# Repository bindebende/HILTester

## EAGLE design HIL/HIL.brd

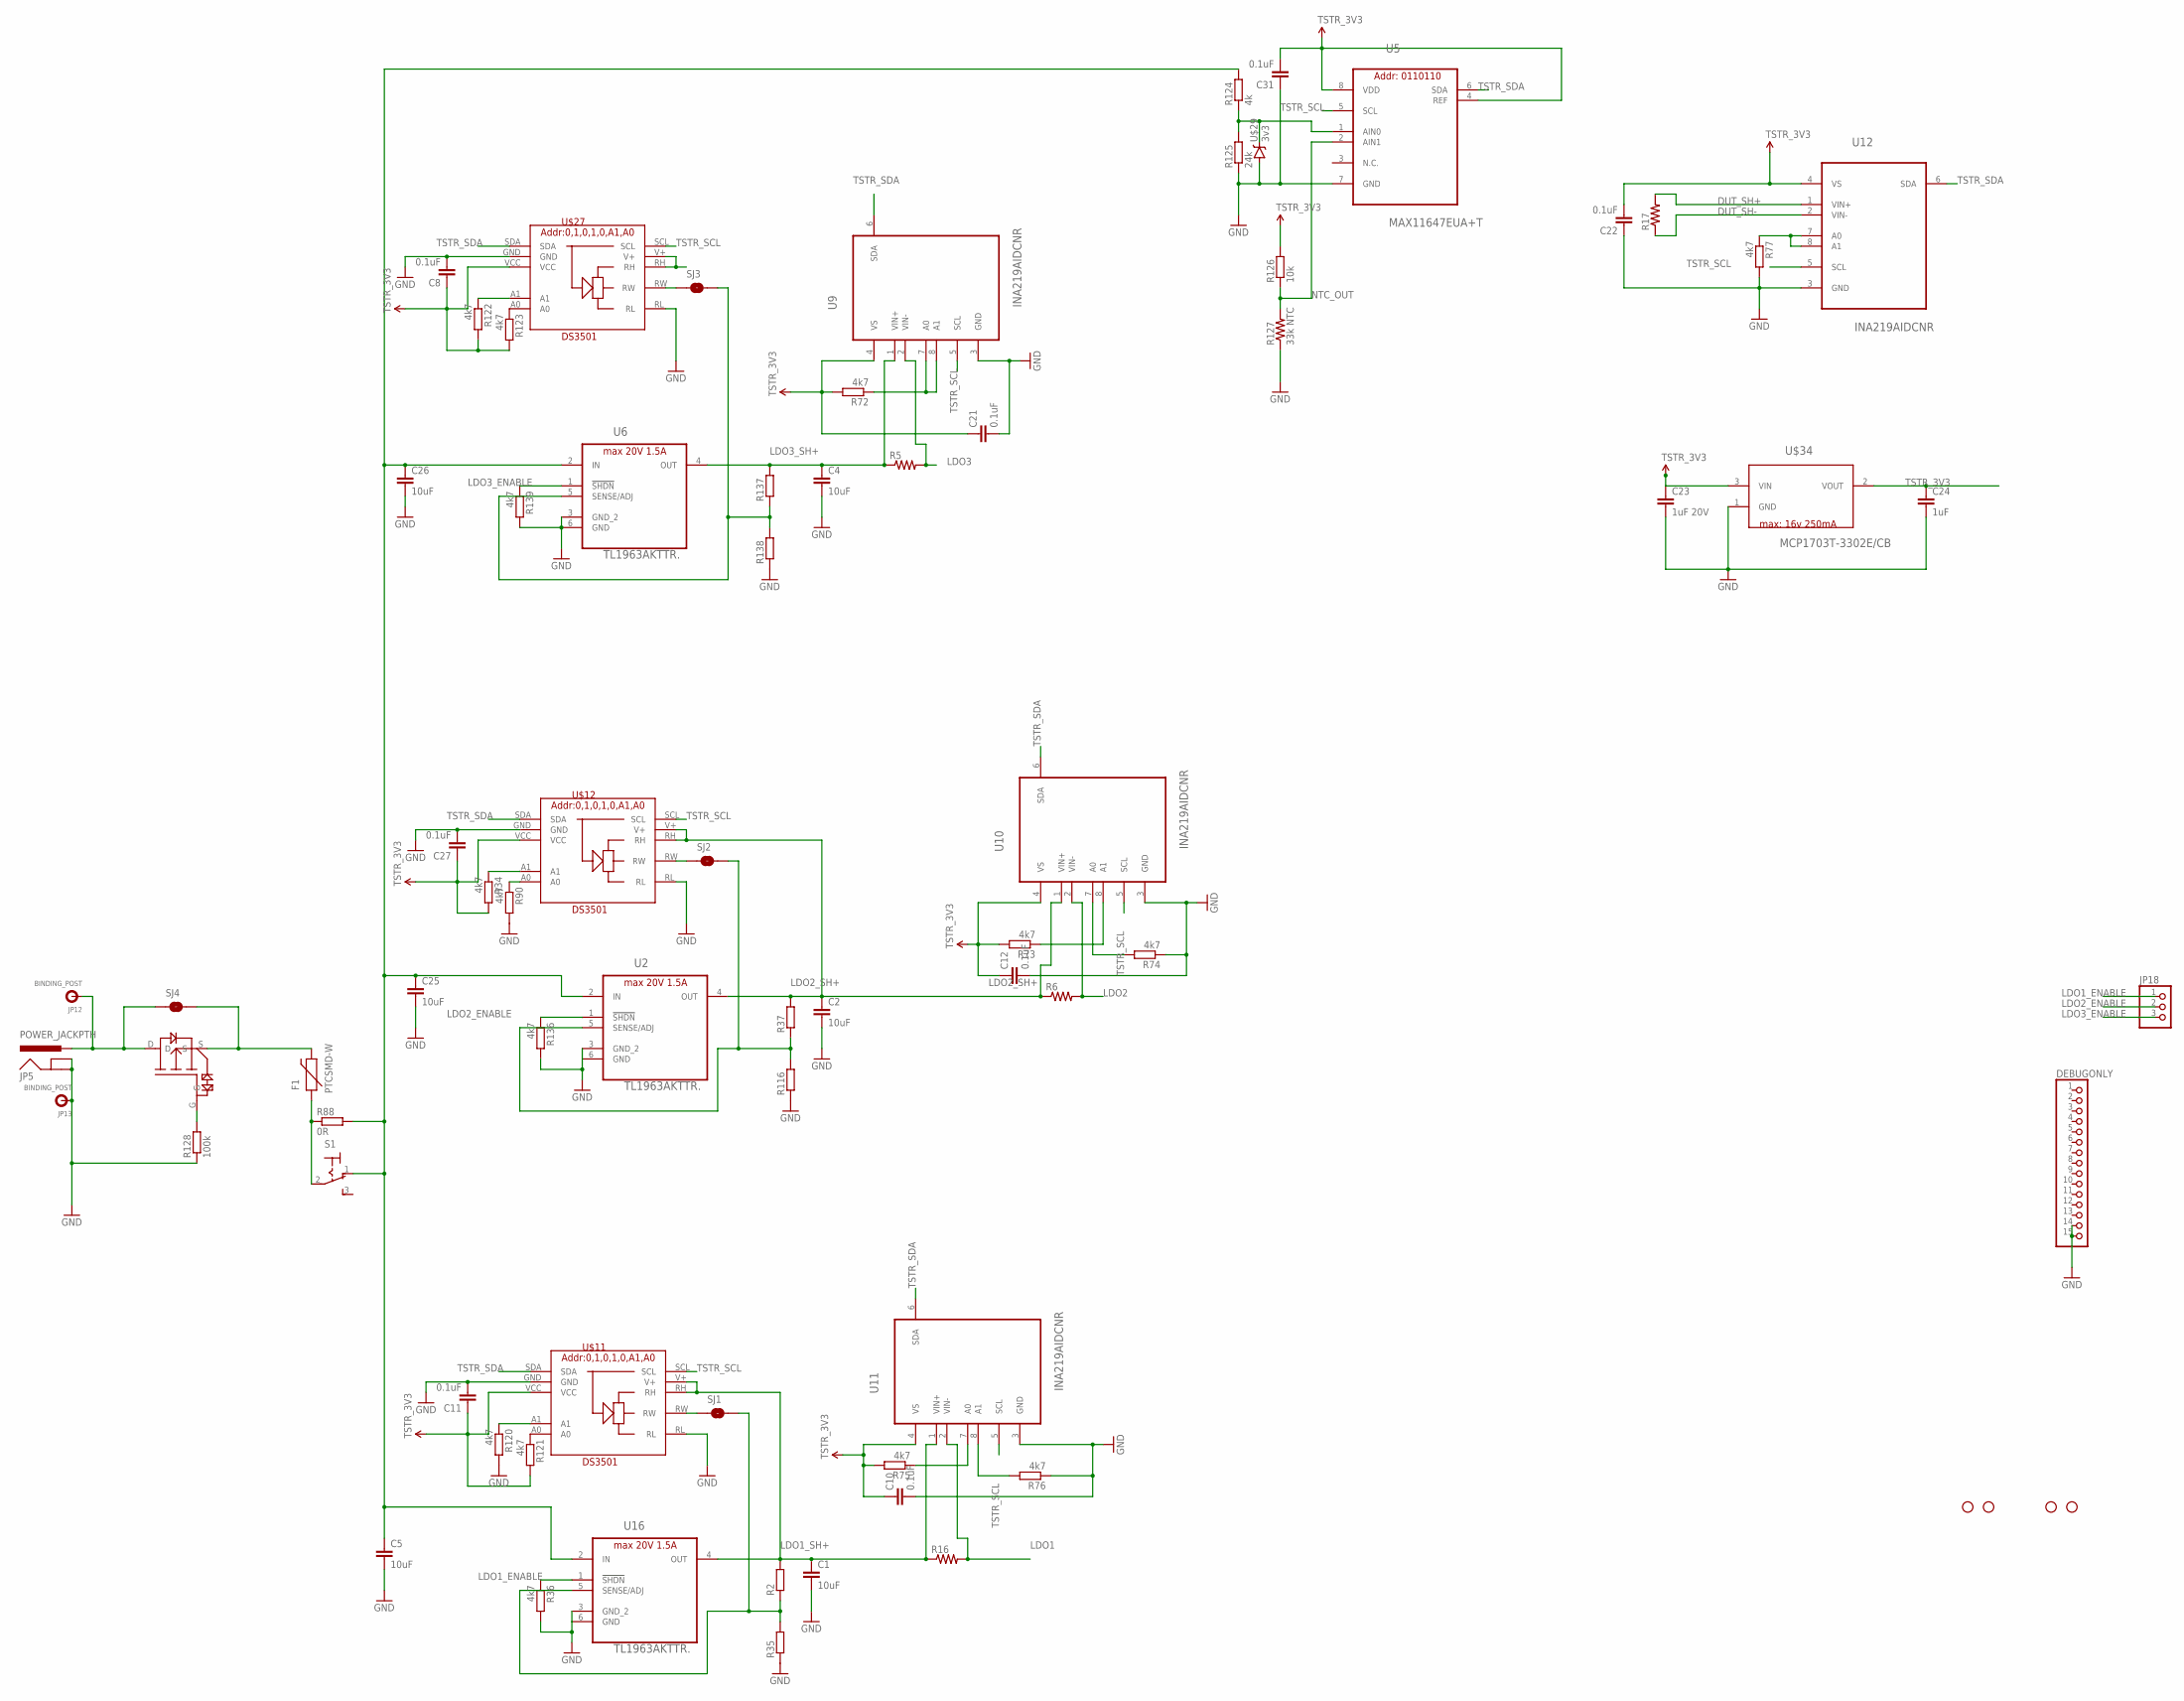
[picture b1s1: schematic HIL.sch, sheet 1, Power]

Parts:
C1, C2, C4, C5, C25, C26: 10uF; C0402
C8, C10, C11, C12, C21, C22, C27, C31: 0.1uF; C0402
C23: 1uF 20V; C0402
C24: 1uF; C0402
DEBUGONLY: PINHD-1X15; 1X15
F1: PTCSMD-W; PTC-1206-WIDE
JP5: POWER_JACKPTH; POWER_JACK_PTH
JP12, JP13: BINDING_POST
JP18: PINHD-1X3CB; 1X03-CLEANBIG
R2, R35, R37, R116, R137, R138: R-EU_R0402; R0402
R5, R6, R16, R17: R-US_R5025; R5025
R34, R36, R72, R73, R74, R75, R76, R77, R90, R120, R121, R122, R123, R136, R139: 4k7; R0402
R88: 0R; R0402
R124: 4k; R0402
R125: 24k; R0402
R126: 10k; R0402
R127: 33k NTC; 1206
R128: 100k; R0402
S1: 320-916
SJ1, SJ2, SJ3, SJ4: SOLDERJUMPERROUND; SJ_ROUND
STANDOFF2, STANDOFF3, STANDOFF4, STANDOFF6: STAND-OFF
U2, U6, U16: TL1963AKTTR.; TO170P1485X457-6N
U5: MAX11647EUA+T; SOP65P490X110-8N
U9, U10, U11, U12: INA219AIDCNR; SOT65P280X145-8N
U$11, U$12, U$27: DS3501
U$29: 3v3; SOT23-3
U$31: ATP101; ATPACK
U$34: MCP1703T-3302E/CB; SOT95P300X145-3N

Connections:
AS: R72.1, U9.7 (A0), U9.8 (A1)
DUT_SH+: R17.2, U12.1 (VIN+); also elsewhere on the board
DUT_SH-: R17.1, U12.2 (VIN-); also elsewhere on the board
GND: C1.2, C2.2, C4.2, C5.2, C8.2, C10.2, C11.2, C12.2, C21.2, C22.1, C23.2, C24.2, C25.2, C26.2, C27.2, C31.1, DEBUGONLY.14, DEBUGONLY.15, JP5.GND, JP5.GNDBREAK, JP13.P$1, R35.1, R36.2, R74.1, R76.1, R77.2, R90.2, R116.1, R120.2, R125.1, R127.1, R128.1, R136.2, R138.1, R139.2, U2.3 (GND_2), U2.6 (GND), U5.7 (GND), U6.3 (GND_2), U6.6 (GND), U9.3 (GND), U10.3 (GND), U11.3 (GND), U12.3 (GND), U16.3 (GND_2), U16.6 (GND), U$11.GND, U$11.RL, U$12.GND, U$12.RL, U$27.GND, U$27.RL, U$29.2 (A), U$34.1 (GND); also elsewhere on the board
LDO1: R16.2, U11.2 (VIN-); also elsewhere on the board
LDO1_ADJ: R2.1, R35.2, SJ1.2, U16.5 (SENSE/ADJ)
LDO1_ENABLE: JP18.1, R36.1, U16.1 (!SHDN)
LDO1_RW: SJ1.1, U$11.RW
LDO1_SH+: C1.1, R2.2, R16.1, U11.1 (VIN+), U16.4 (OUT), U$11.RH, U$11.V+; also elsewhere on the board
LDO2: R6.2, U10.2 (VIN-); also elsewhere on the board
LDO2_ADJ: R37.1, R116.2, SJ2.2, U2.5 (SENSE/ADJ)
LDO2_ENABLE: JP18.2, R136.1, U2.1 (!SHDN)
LDO2_RW: SJ2.1, U$12.RW
LDO2_SH+: C2.1, R6.1, R37.2, U2.4 (OUT), U10.1 (VIN+), U$12.RH, U$12.V+; also elsewhere on the board
LDO3: R5.2, U9.2 (VIN-); also elsewhere on the board
LDO3_ADJ: R137.1, R138.2, SJ3.2, U6.5 (SENSE/ADJ)
LDO3_ENABLE: JP18.3, R139.1, U6.1 (!SHDN)
LDO3_RW: SJ3.1, U$27.RW
LDO3_SH+: C4.1, R5.1, R137.2, U6.4 (OUT), U9.1 (VIN+); also elsewhere on the board
unnamed: F1.1, R88.1, S1.2
unnamed: R128.2, U$31.G
unnamed: R73.1, U10.8 (A1)
unnamed: R75.1, U11.7 (A0)
unnamed: R74.2, U10.7 (A0)
unnamed: R76.2, U11.8 (A1)
unnamed: R77.1, U12.7 (A0), U12.8 (A1)
unnamed: R120.1, U$11.A1
unnamed: R121.1, U$11.A0
unnamed: R34.1, U$12.A1
unnamed: R90.1, U$12.A0
unnamed: R122.1, U$27.A1
unnamed: R123.1, U$27.A0
unnamed: U$27.RH, U$27.V+
NTC_OUT: R126.1, R127.2, U5.2 (AIN1)
POWER_IN_12V: C5.1, C23.1, C25.1, C26.1, R88.2, R124.2, S1.1 (O), U2.2 (IN), U6.2 (IN), U16.2 (IN), U$34.3 (VIN); also elsewhere on the board
SUPPLY_DIV: R124.1, R125.2, U5.1 (AIN0), U$29.1 (C)
TSTR_3V3: C8.1, C10.1, C11.1, C12.1, C21.1, C22.2, C24.1, C27.1, C31.2, R34.2, R72.2, R73.2, R75.2, R121.2, R122.2, R123.2, R126.2, U5.4 (REF), U5.8 (VDD), U9.4 (VS), U10.4 (VS), U11.4 (VS), U12.4 (VS), U$11.VCC, U$12.VCC, U$27.VCC, U$34.2 (VOUT); also elsewhere on the board
TSTR_SCL: U5.5 (SCL), U9.5 (SCL), U10.5 (SCL), U11.5 (SCL), U12.5 (SCL), U$11.SCL, U$12.SCL, U$27.SCL; also elsewhere on the board
TSTR_SDA: U5.6 (SDA), U9.6 (SDA), U10.6 (SDA), U11.6 (SDA), U12.6 (SDA), U$11.SDA, U$12.SDA, U$27.SDA; also elsewhere on the board
VIN: F1.2, SJ4.2, U$31.S
VIN_REV: JP5.PWR, JP12.P$1, SJ4.1, U$31.D

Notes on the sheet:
max: 16v 250mA

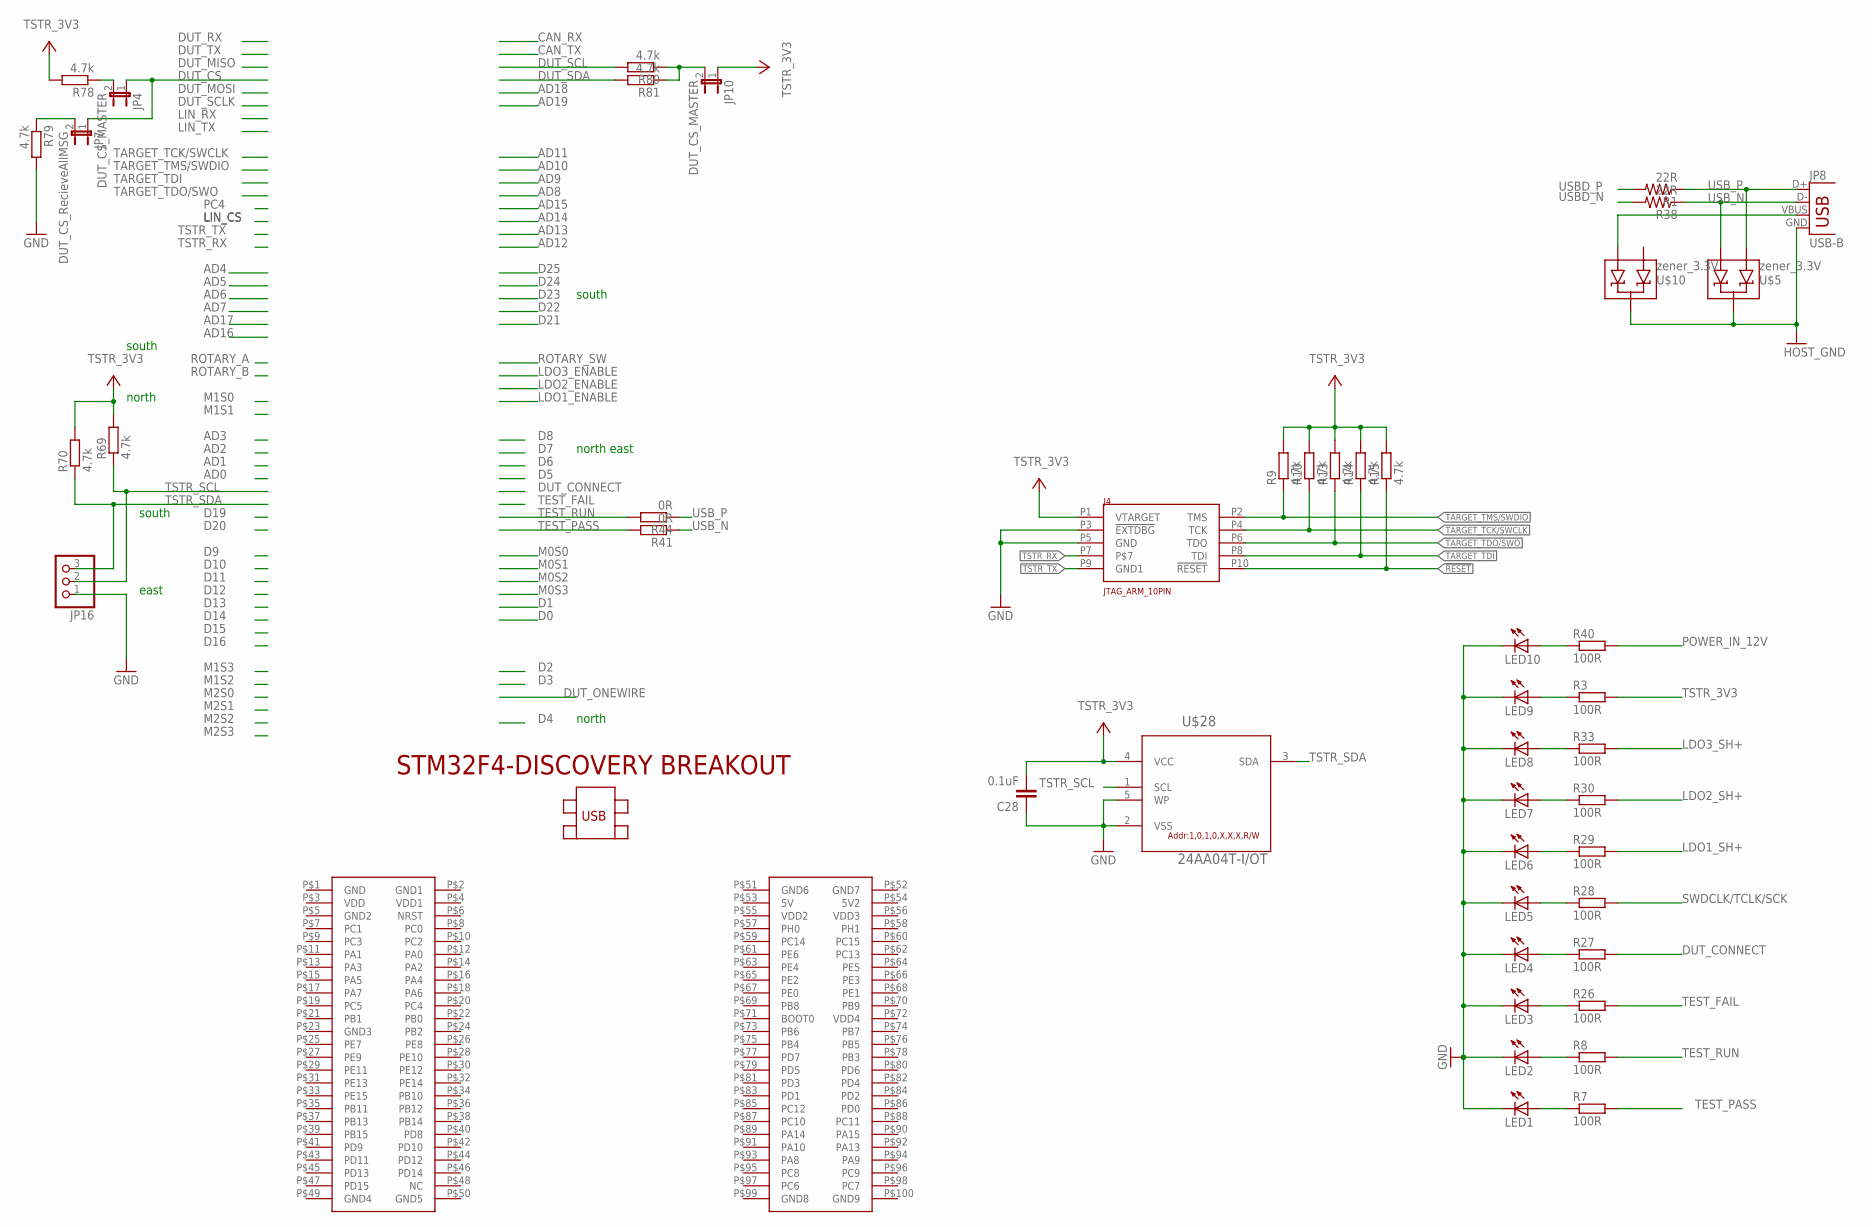
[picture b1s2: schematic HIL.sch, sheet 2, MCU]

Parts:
C28: 0.1uF; C0402K
J4: JTAG_ARM_10PIN; CON_2X5_50MIL
JP4, JP10: DUT_CS_MASTER; SJ_2S-NO
JP7: DUT_CS_RecieveAllMSG; SJ_2S-NO
JP8: USB-B; USB-B-PTH
JP16: PINHD-1X3CB; 1X03-CLEANBIG
LED1, LED2, LED3, LED4, LED5, LED6, LED7, LED8, LED9, LED10: LEDCHIP-LED0805; CHIP-LED0805
R1, R38: 22R; 0402-RES
R3, R7, R8, R26, R27, R28, R29, R30, R33, R40: 100R; R0402
R9, R10, R13, R14, R15, R69, R70, R78, R79, R80, R81: 4.7k; R0402
R41, R44: 0R; R0402
U$5, U$10: zener_3.3V; SOT23-3
U$28: 24AA04T-I/OT; SOT95P290X145-5N
U$30: STM32F4-DISCOVERY_STM32F4-DISCOVERY

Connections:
!RESET: J4.P10 (!RESET), R15.1
DUT_CONNECT: R27.2
DUT_CS: JP4.1, JP7.1; also elsewhere on the board
DUT_SCL: R80.2; also elsewhere on the board
DUT_SDA: R81.2; also elsewhere on the board
GND: C28.1, J4.P3 (!EXTDBG), J4.P5 (GND), JP16.1, LED1.C, LED2.C, LED3.C, LED4.C, LED5.C, LED6.C, LED7.C, LED8.C, LED9.C, LED10.C, R79.2, U$28.2 (VSS), U$28.5 (WP); also elsewhere on the board
HOST_GND: JP8.GND, U$5.3 (C), U$10.3 (C)
LDO1_SH+: R29.2; also elsewhere on the board
LDO2_SH+: R30.2; also elsewhere on the board
LDO3_SH+: R33.2; also elsewhere on the board
unnamed: LED2.A, R8.1
unnamed: LED1.A, R7.1
unnamed: LED3.A, R26.1
unnamed: LED4.A, R27.1
unnamed: LED5.A, R28.1
unnamed: LED6.A, R29.1
unnamed: LED7.A, R30.1
unnamed: LED8.A, R33.1
unnamed: JP7.2, R79.1
unnamed: JP10.2, R80.1, R81.1
unnamed: JP8.VBUS, U$10.1 (A1)
unnamed: LED9.A, R3.1
unnamed: LED10.A, R40.1
POWER_IN_12V: R40.2; also elsewhere on the board
SWDCLK/TCLK/SCK: R28.2; also elsewhere on the board
TARGET_TCK/SWCLK: J4.P4 (TCK), R10.1
TARGET_TDI: J4.P8 (TDI), R14.1
TARGET_TDO/SWO: J4.P6 (TDO), R13.1
TARGET_TMS/SWDIO: J4.P2 (TMS), R9.1
TEST_FAIL: R26.2
TEST_PASS: R7.2, R41.2
TEST_RUN: R8.2, R44.2
TSTR_3V3: C28.2, J4.P1 (VTARGET), JP10.1, R3.2, R9.2, R10.2, R13.2, R14.2, R15.2, R69.2, R70.2, R78.2, U$28.4 (VCC); also elsewhere on the board
TSTR_RX: J4.P7
TSTR_SCL: JP16.2, R69.1, U$28.1 (SCL); also elsewhere on the board
TSTR_SCL1: JP4.2, R78.1
TSTR_SDA: JP16.3, R70.1, U$28.3 (SDA); also elsewhere on the board
TSTR_TX: J4.P9 (GND1)
USBD_N: R38.2
USBD_P: R1.2
USB_N: JP8.D-, R38.1, R41.1, U$5.1 (A1)
USB_P: JP8.D+, R1.1, R44.1, U$5.2 (A2)

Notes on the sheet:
south
north east
north
east

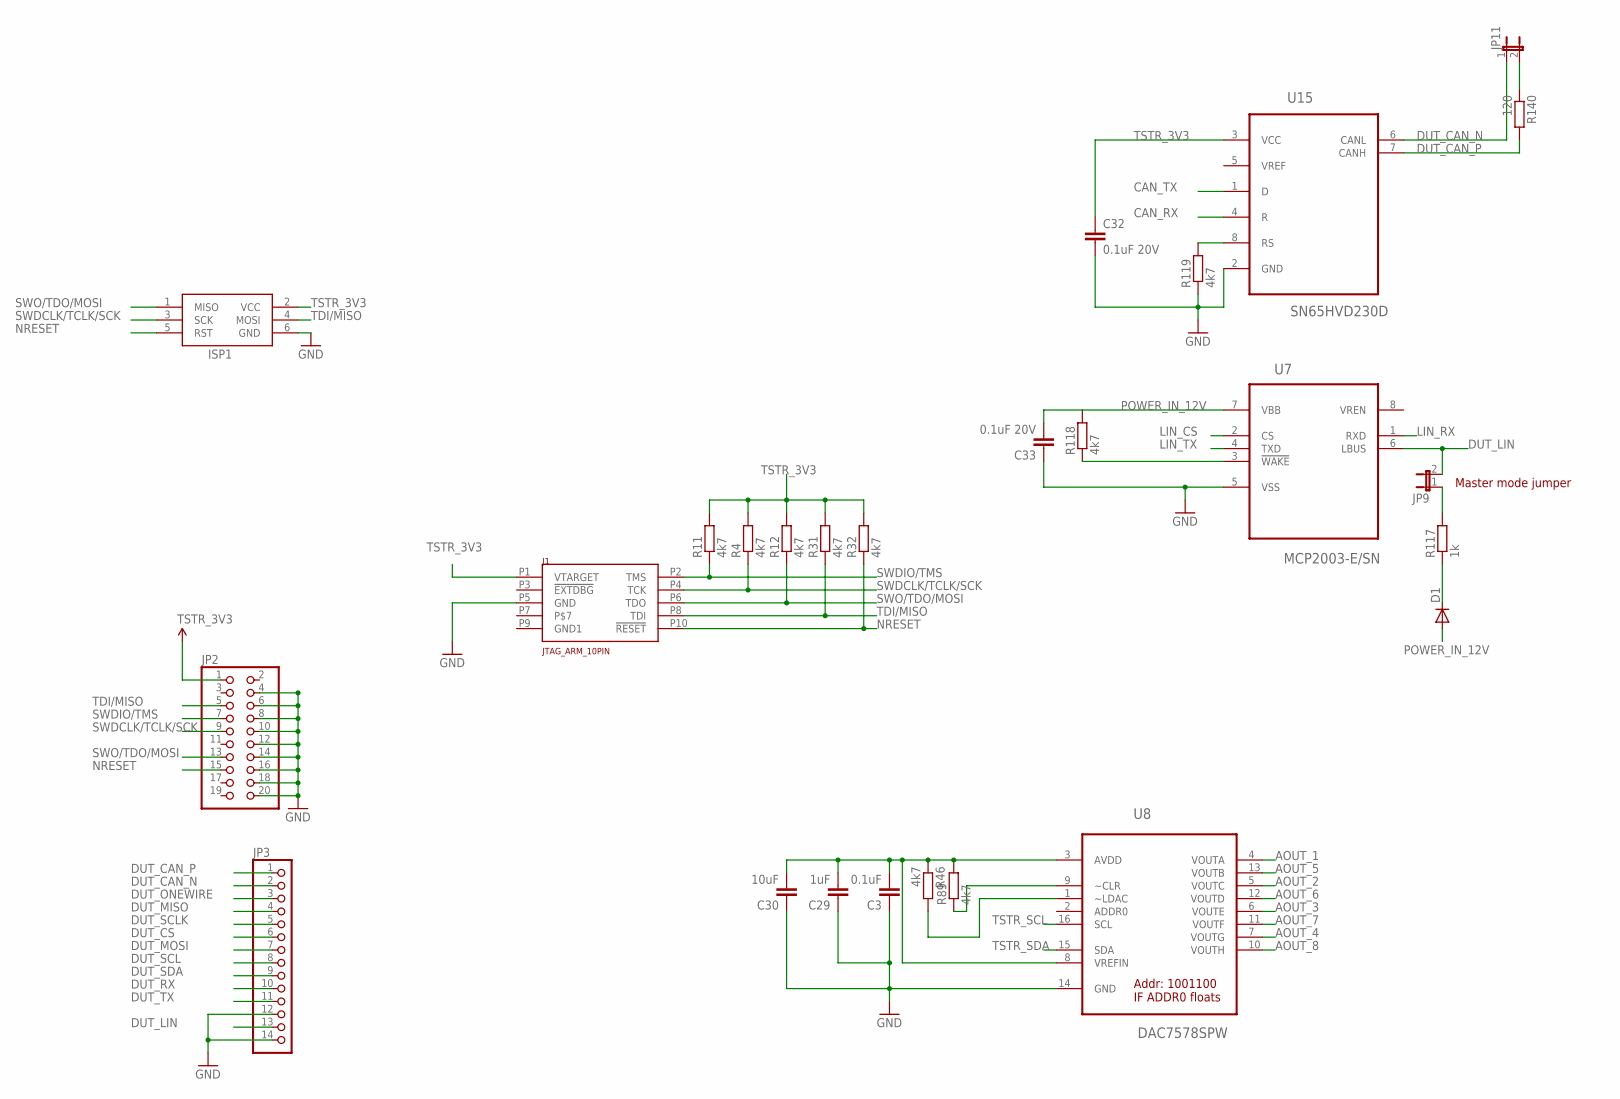
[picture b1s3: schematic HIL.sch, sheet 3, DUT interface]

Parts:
C3: 0.1uF; C0402K
C29: 1uF; C0402K
C30: 10uF; C0402K
C32, C33: 0.1uF 20V; C0402K
D1: DIODE-SOD523; SOD523
ISP1: AVRISP-6; AVRISP
J1: JTAG_ARM_10PIN; CON_2X5_50MIL
JP2: PINHD-2X10; 2X10
JP3: PINHD-1X14; 1X14
JP9: JUMPER-2SMD-NC; SJ_2S
JP11: JUMPER-2SMD-NO; SJ_2S-NO
R4, R11, R12, R31, R32, R46, R89, R118, R119: 4k7; R0402
R117: 1k; R0402
R140: 120; R0402
U7: MCP2003-E/SN; SOIC127P600X175-8N
U8: DAC7578SPW; SOP65P640X120-16N
U15: SN65HVD230D; SOIC127P600X175-8N

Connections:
AOUT_1: U8.4 (VOUTA); also elsewhere on the board
AOUT_2: U8.5 (VOUTC); also elsewhere on the board
AOUT_3: U8.6 (VOUTE); also elsewhere on the board
AOUT_4: U8.7 (VOUTG); also elsewhere on the board
AOUT_5: U8.13 (VOUTB); also elsewhere on the board
AOUT_6: U8.12 (VOUTD); also elsewhere on the board
AOUT_7: U8.11 (VOUTF); also elsewhere on the board
AOUT_8: U8.10 (VOUTH); also elsewhere on the board
CAN_RX: U15.4 (R)
CAN_TX: U15.1 (D)
DUT_CAN_N: JP3.2, JP11.1, U15.6 (CANL); also elsewhere on the board
DUT_CAN_P: JP3.1, R140.2, U15.7 (CANH); also elsewhere on the board
DUT_CS: JP3.6; also elsewhere on the board
DUT_LIN: JP3.13, JP9.2, U7.6 (LBUS); also elsewhere on the board
DUT_MISO: JP3.4; also elsewhere on the board
DUT_MOSI: JP3.7; also elsewhere on the board
DUT_ONEWIRE: JP3.3; also elsewhere on the board
DUT_RX: JP3.10; also elsewhere on the board
DUT_SCL: JP3.8; also elsewhere on the board
DUT_SCLK: JP3.5; also elsewhere on the board
DUT_SDA: JP3.9; also elsewhere on the board
DUT_TX: JP3.11; also elsewhere on the board
GND: C3.1, C29.1, C30.1, C32.2, C33.1, ISP1.6 (GND), J1.P5 (GND), JP2.4, JP2.6, JP2.8, JP2.10, JP2.12, JP2.14, JP2.16, JP2.18, JP2.20, JP3.12, JP3.14, R119.1, U7.5 (VSS), U8.14 (GND), U15.2 (GND); also elsewhere on the board
LIN_CS: U7.2 (CS)
LIN_RX: U7.1 (RXD)
LIN_TX: U7.4 (TXD)
unnamed: R46.2, U8.1 (~LDAC)
unnamed: JP11.2, R140.1
unnamed: C3.2, C29.2, C30.2, R46.1, R89.2, U8.3 (AVDD), U8.8 (VREFIN)
unnamed: D1.C, R117.1
unnamed: R118.1, U7.3 (!WAKE)
unnamed: JP9.1, R117.2
unnamed: R89.1, U8.9 (~CLR)
unnamed: R119.2, U15.8 (RS)
NRESET: ISP1.5 (RST), J1.P10 (!RESET), JP2.15, R32.1; also elsewhere on the board
POWER_IN_12V: C33.2, D1.A, R118.2, U7.7 (VBB); also elsewhere on the board
SWDCLK/TCLK/SCK: ISP1.3 (SCK), J1.P4 (TCK), JP2.9, R4.1; also elsewhere on the board
SWDIO/TMS: J1.P2 (TMS), JP2.7, R11.1; also elsewhere on the board
SWO/TDO/MOSI: ISP1.1 (MISO), J1.P6 (TDO), JP2.13, R12.1; also elsewhere on the board
TDI/MISO: ISP1.4 (MOSI), J1.P8 (TDI), JP2.5, R31.1; also elsewhere on the board
TSTR_3V3: C32.1, ISP1.2 (VCC), J1.P1 (VTARGET), JP2.1, R4.2, R11.2, R12.2, R31.2, R32.2, U15.3 (VCC); also elsewhere on the board
TSTR_SCL: U8.16 (SCL); also elsewhere on the board
TSTR_SDA: U8.15 (SDA); also elsewhere on the board
VREN: U7.8 (VREN)

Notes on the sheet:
Master mode jumper

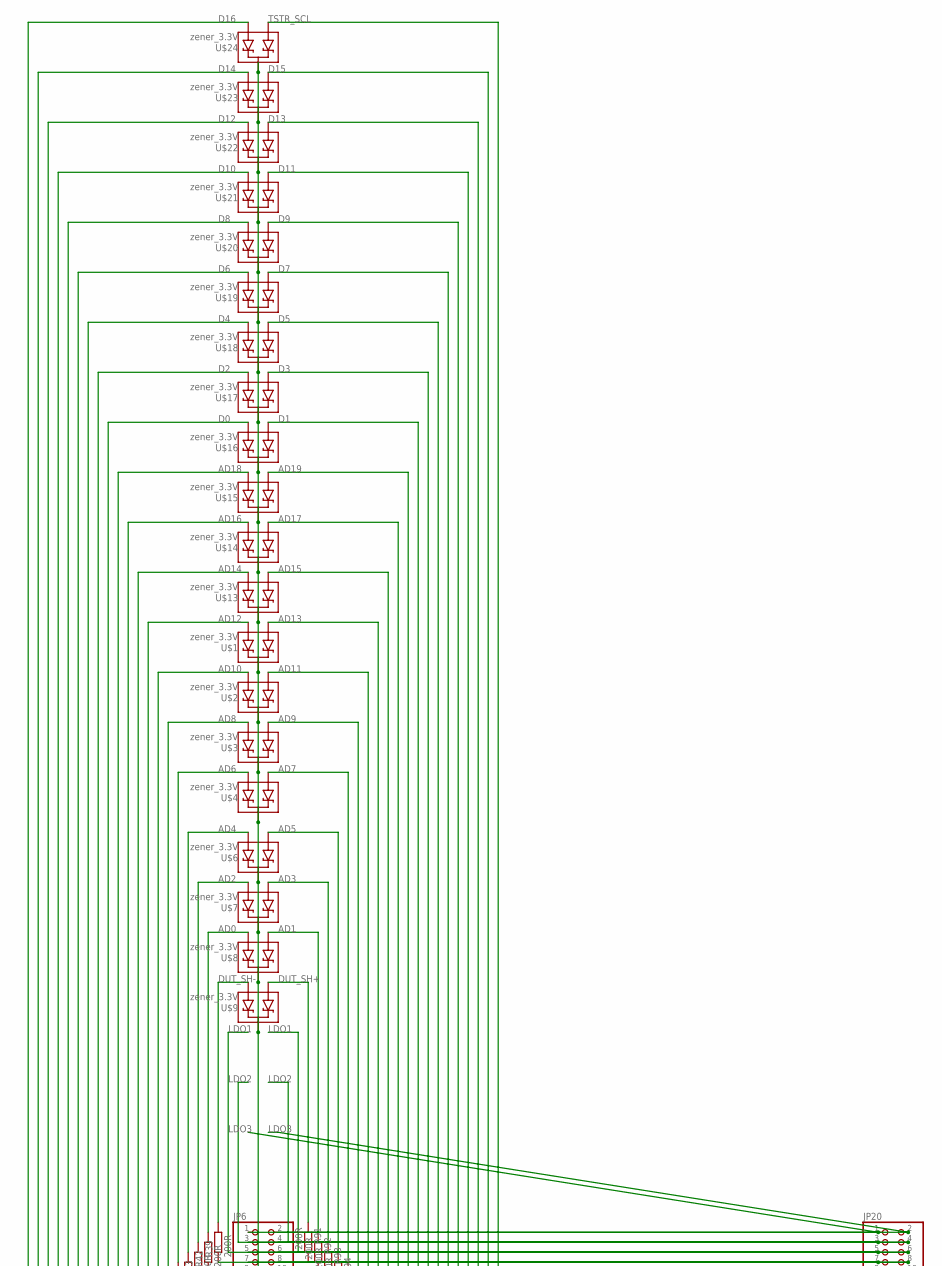
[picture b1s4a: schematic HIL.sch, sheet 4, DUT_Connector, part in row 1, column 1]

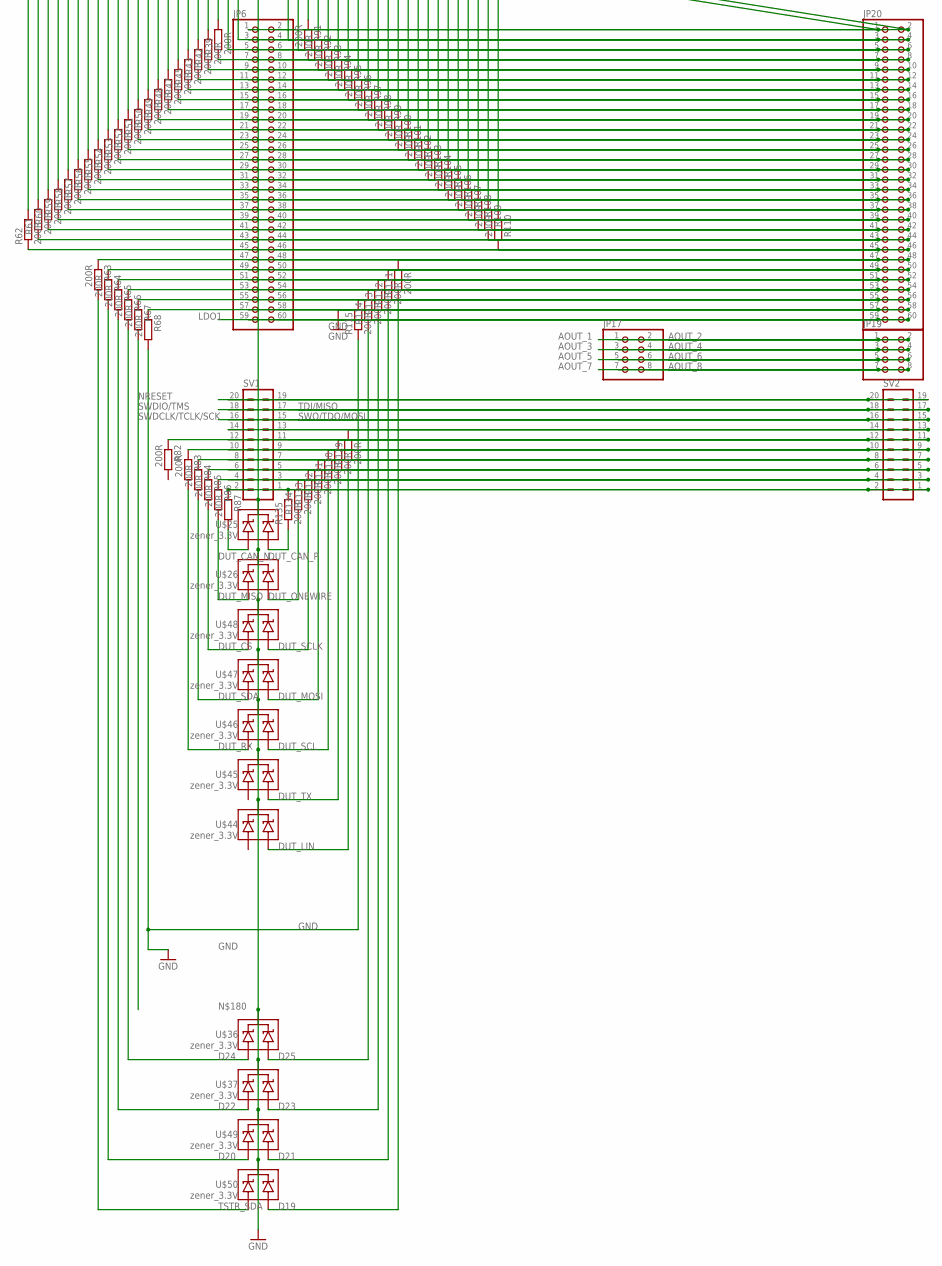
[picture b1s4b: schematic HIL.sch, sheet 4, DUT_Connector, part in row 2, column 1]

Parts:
JP6, JP20: PINHD-2X30; 2X30
JP17, JP19: PINHD-2X4; 2X04
R39, R42, R43, R45, R47, R48, R49, R50, R51, R52, R53, R54, R55, R56, R57, R58, R59, R60, R61, R62, R63, R64, R65, R66, R67, R68, R82, R83, R84, R85, R86, R87, R91, R92, R93, R94, R95, R96, R97, R98, R99, R100, R101, R102, R103, R104, R105, R106, R107, R108, R109, R110, R111, R112, R113, R114, R115, R129, R130, R131, R132, R133, R134, R135: 200R; R0402
SV1, SV2: MA10-2
U$1, U$2, U$3, U$4, U$6, U$7, U$8, U$9, U$13, U$14, U$15, U$16, U$17, U$18, U$19, U$20, U$21, U$22, U$23, U$24, U$25, U$26, U$36, U$37, U$44, U$45, U$46, U$47, U$48, U$49, U$50: zener_3.3V; SOT23-3

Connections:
AD0: R42.2, U$8.2 (A2); also elsewhere on the board
AD1: R92.1, U$8.1 (A1); also elsewhere on the board
AD2: R43.2, U$7.2 (A2); also elsewhere on the board
AD3: R93.1, U$7.1 (A1); also elsewhere on the board
AD4: R45.2, U$6.2 (A2); also elsewhere on the board
AD5: R94.1, U$6.1 (A1); also elsewhere on the board
AD6: R47.2, U$4.2 (A2); also elsewhere on the board
AD7: R95.1, U$4.1 (A1); also elsewhere on the board
AD8: R48.2, U$3.2 (A2); also elsewhere on the board
AD9: R96.1, U$3.1 (A1); also elsewhere on the board
AD10: R49.2, U$2.2 (A2); also elsewhere on the board
AD11: R97.1, U$2.1 (A1); also elsewhere on the board
AD12: R50.2, U$1.2 (A2); also elsewhere on the board
AD13: R98.1, U$1.1 (A1); also elsewhere on the board
AD14: R51.2, U$13.2 (A2); also elsewhere on the board
AD15: R99.1, U$13.1 (A1); also elsewhere on the board
AD16: R52.2, U$14.2 (A2); also elsewhere on the board
AD17: R100.1, U$14.1 (A1); also elsewhere on the board
AD18: R53.2, U$15.2 (A2); also elsewhere on the board
AD19: R101.1, U$15.1 (A1); also elsewhere on the board
AOUT_1: JP17.1, JP19.1; also elsewhere on the board
AOUT_2: JP17.2, JP19.2; also elsewhere on the board
AOUT_3: JP17.3, JP19.3; also elsewhere on the board
AOUT_4: JP17.4, JP19.4; also elsewhere on the board
AOUT_5: JP17.5, JP19.5; also elsewhere on the board
AOUT_6: JP17.6, JP19.6; also elsewhere on the board
AOUT_7: JP17.7, JP19.7; also elsewhere on the board
AOUT_8: JP17.8, JP19.8; also elsewhere on the board
D0: R54.2, U$16.2 (A2); also elsewhere on the board
D1: R102.1, U$16.1 (A1); also elsewhere on the board
D2: R55.2, U$17.2 (A2); also elsewhere on the board
D3: R103.1, U$17.1 (A1); also elsewhere on the board
D4: R56.2, U$18.2 (A2); also elsewhere on the board
D5: R104.1, U$18.1 (A1); also elsewhere on the board
D6: R57.2, U$19.2 (A2); also elsewhere on the board
D7: R105.1, U$19.1 (A1); also elsewhere on the board
D8: R58.2, U$20.2 (A2); also elsewhere on the board
D9: R106.1, U$20.1 (A1); also elsewhere on the board
D10: R59.2, U$21.2 (A2); also elsewhere on the board
D11: R107.1, U$21.1 (A1); also elsewhere on the board
D12: R60.2, U$22.2 (A2); also elsewhere on the board
D13: R108.1, U$22.1 (A1); also elsewhere on the board
D14: R61.2, U$23.2 (A2); also elsewhere on the board
D15: R109.1, U$23.1 (A1); also elsewhere on the board
D16: R62.2, U$24.2 (A2); also elsewhere on the board
D19: R111.1, U$50.1 (A1); also elsewhere on the board
D20: R64.2, U$49.2 (A2); also elsewhere on the board
D21: R112.1, U$49.1 (A1); also elsewhere on the board
D22: R65.2, U$37.2 (A2); also elsewhere on the board
D23: R113.1, U$37.1 (A1); also elsewhere on the board
D24: R66.2, U$36.2 (A2); also elsewhere on the board
D25: R114.1, U$36.1 (A1); also elsewhere on the board
DUT_CAN_N: R87.2, U$25.2 (A2); also elsewhere on the board
DUT_CAN_P: R135.1, U$25.1 (A1); also elsewhere on the board
DUT_CS: R85.2, U$48.2 (A2); also elsewhere on the board
DUT_LIN: R129.1, U$44.1 (A1); also elsewhere on the board
DUT_MISO: R86.2, U$26.2 (A2); also elsewhere on the board
DUT_MOSI: R132.1, U$47.1 (A1); also elsewhere on the board
DUT_ONEWIRE: R134.1, U$26.1 (A1); also elsewhere on the board
DUT_RX: R83.2, U$46.2 (A2); also elsewhere on the board
DUT_SCL: R131.1, U$46.1 (A1); also elsewhere on the board
DUT_SCLK: R133.1, U$48.1 (A1); also elsewhere on the board
DUT_SDA: R84.2, U$47.2 (A2); also elsewhere on the board
DUT_SH+: R91.1, U$9.1 (A1); also elsewhere on the board
DUT_SH-: R39.2, U$9.2 (A2); also elsewhere on the board
DUT_TX: R130.1, U$45.1 (A1); also elsewhere on the board
GND: JP6.58, JP6.60, JP20.58, JP20.60, R68.2, R115.1, U$1.3 (C), U$2.3 (C), U$3.3 (C), U$4.3 (C), U$6.3 (C), U$7.3 (C), U$8.3 (C), U$9.3 (C), U$13.3 (C), U$14.3 (C), U$15.3 (C), U$16.3 (C), U$17.3 (C), U$18.3 (C), U$19.3 (C), U$20.3 (C), U$21.3 (C), U$22.3 (C), U$23.3 (C), U$24.3 (C), U$25.3 (C), U$26.3 (C), U$36.3 (C), U$37.3 (C), U$44.3 (C), U$45.3 (C), U$46.3 (C), U$47.3 (C), U$48.3 (C), U$49.3 (C), U$50.3 (C); also elsewhere on the board
LDO1: JP6.5, JP6.6, JP6.59, JP20.5, JP20.6, JP20.59; also elsewhere on the board
LDO2: JP6.3, JP6.4, JP20.3, JP20.4; also elsewhere on the board
LDO3: JP6.1, JP6.2, JP20.1, JP20.2; also elsewhere on the board
unnamed: R87.1, SV1.2, SV2.2
unnamed: R135.2, SV1.1, SV2.1
unnamed: JP6.7, JP20.7, R39.1
unnamed: JP6.9, JP20.9, R42.1
unnamed: JP6.11, JP20.11, R43.1
unnamed: JP6.13, JP20.13, R45.1
unnamed: JP6.15, JP20.15, R47.1
unnamed: JP6.17, JP20.17, R48.1
unnamed: JP6.19, JP20.19, R49.1
unnamed: JP6.21, JP20.21, R50.1
unnamed: JP6.23, JP20.23, R51.1
unnamed: JP6.25, JP20.25, R52.1
unnamed: JP6.27, JP20.27, R53.1
unnamed: JP6.29, JP20.29, R54.1
unnamed: JP6.31, JP20.31, R55.1
unnamed: JP6.33, JP20.33, R56.1
unnamed: JP6.35, JP20.35, R57.1
unnamed: JP6.37, JP20.37, R58.1
unnamed: JP6.39, JP20.39, R59.1
unnamed: JP6.41, JP20.41, R60.1
unnamed: JP6.43, JP20.43, R61.1
unnamed: JP6.45, JP20.45, R62.1
unnamed: JP6.47, JP20.47, R63.1
unnamed: JP6.49, JP20.49, R64.1
unnamed: JP6.51, JP20.51, R65.1
unnamed: JP6.53, JP20.53, R66.1
unnamed: JP6.55, JP20.55, R67.1
unnamed: JP6.57, JP20.57, R68.1
unnamed: SV1.14, SV2.14
unnamed: R82.1, SV1.12, SV2.12
unnamed: R83.1, SV1.10, SV2.10
unnamed: R84.1, SV1.8, SV2.8
unnamed: R85.1, SV1.6, SV2.6
unnamed: R86.1, SV1.4, SV2.4
unnamed: SV1.19, SV2.19
unnamed: R129.2, SV1.13, SV2.13
unnamed: R130.2, SV1.11, SV2.11
unnamed: R131.2, SV1.9, SV2.9
unnamed: R132.2, SV1.7, SV2.7
unnamed: R133.2, SV1.5, SV2.5
unnamed: R134.2, SV1.3, SV2.3
unnamed: JP6.8, JP20.8, R91.2
unnamed: JP6.10, JP20.10, R92.2
unnamed: JP6.12, JP20.12, R93.2
unnamed: JP6.14, JP20.14, R94.2
unnamed: JP6.16, JP20.16, R95.2
unnamed: JP6.18, JP20.18, R96.2
unnamed: JP6.20, JP20.20, R97.2
unnamed: JP6.22, JP20.22, R98.2
unnamed: JP6.24, JP20.24, R99.2
unnamed: JP6.26, JP20.26, R100.2
unnamed: JP6.28, JP20.28, R101.2
unnamed: JP6.30, JP20.30, R102.2
unnamed: JP6.32, JP20.32, R103.2
unnamed: JP6.34, JP20.34, R104.2
unnamed: JP6.36, JP20.36, R105.2
unnamed: JP6.38, JP20.38, R106.2
unnamed: JP6.40, JP20.40, R107.2
unnamed: JP6.42, JP20.42, R108.2
unnamed: JP6.44, JP20.44, R109.2
unnamed: JP6.46, JP20.46, R110.2
unnamed: JP6.48, JP20.48, R111.2
unnamed: JP6.50, JP20.50, R112.2
unnamed: JP6.52, JP20.52, R113.2
unnamed: JP6.54, JP20.54, R114.2
unnamed: JP6.56, JP20.56, R115.2
NRESET: SV1.20, SV2.20; also elsewhere on the board
SWDCLK/TCLK/SCK: SV1.16, SV2.16; also elsewhere on the board
SWDIO/TMS: SV1.18, SV2.18; also elsewhere on the board
SWO/TDO/MOSI: SV1.15, SV2.15; also elsewhere on the board
TDI/MISO: SV1.17, SV2.17; also elsewhere on the board
TSTR_SCL: R110.1, U$24.1 (A1); also elsewhere on the board
TSTR_SDA: R63.2, U$50.2 (A2); also elsewhere on the board

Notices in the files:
parts and their libraries:
SparkFun-Connectors: Licensing: Creative Commons ShareAlike 4.0 International - https://creativecommons.org/licenses/by-sa/4.0
microbuilder: This work is placed in the public domain, and may be freely used for commercial and non-commercial work with the following conditions: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
